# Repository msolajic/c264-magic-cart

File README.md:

# c264-magic-cart
Hardware design of a cartridge for the Commodore 264 series of computers - Commodore 16, 116 and plus/4

This is the hardware part that accompanies the project of [Magic Cartridge Generator](https://bitbucket.org/zzarko/magic-cartridge-generator/)

This project is free to use and you can use any PCB manufacturer by downloading the Gerber files, but if you would like to support my work and help with further hardware development you can order these PCBs on PCBWay trough this link:

You will get cheap and professionally made PCBs, I will get credits that will help with this and [other projects](https://www.pcbway.com/project/member/?bmbno=1DE407A1-1650-47). Also, if you have to register to that site, [you can use this link](https://pcbway.com/g/YFnBAc) to get bonus initial credit.

Hardware Description
--------------------

Original Commodore 264 cartridges could be up to 32 Kb in size, in two separate banks of 16Kb. This cartridge implements a latch which is tied to a memory address, so it can address (in this incarnation) up to 2 megabytes of data (128 banks of 16Kb). In that regard, it is very similar to Magic Desk or Ocean cartridges for the Commodore 64.

EPROM is selected by the C1LO selection line coming from the computer, and the 16k of data from the selected bank is visible in the memory map at addresses $8000 - $BFFF.

Inputs of an 8-bit latch (74LS273) are connected to the data lines. A GAL20V8 is responsible for decoding writes to a memory address by decoding the full address bus. Decoder has the option of decoding several frequently used addresses for banking cartridges, since there is no standard address defined. This cartridge is primarily designed to enable making onefile program compilations through the [Magic Cartridge Generator](https://bitbucket.org/zzarko/magic-cartridge-generator/).

The PCB was designed to accommodate various types of EPROMs and their FLASH variants. The smallest EPROM you can use is 27C010 (128Kb), and the largest is 27C160 (2Mb). There are two EPROM sockets, but you cannot use both at the same time. The left socket accepts standard 8-bit EPROMs and their FLASH variants (27C010 to 27C080) and the right socket is for 27C160 (16-bit EPROM in 8-bit mode).

Address decoder
---------------

The address decoder is implemented in GAL20V8. All 16 address lines, /PHI2 and /RW are connected to the GAL to enable single-address decoding. Of course, a GAL16V8 could have been used, but it would only be capable of decoding an address in 16-byte blocks, or the address decoder could be implemented in TTL logic which would require at least 3 ICs. Two spare inputs were used to create a selection jumper to select between four commonly used addresses for cartridge banking. The default address used is $FDFE, which is mentioned in the document at http://solder-synergy.de/plus4/hardware/makers/ioarea.txt as "Register on EPROM-card". Other addresses which can be configured are $FE00 (used on a Hungarian homebrew cartridge found at https://www.commodoreszerviz.hu/commodore_16-116-plus_4_1mb_cartridge_juhasz_jacint.htm), $FDA0 used by another homebrew cartridge, and $FD17 which is also mentioned in the document above as "Register for EPROM-/sRAM-expansion". 

The address decoder is configured with a solder-jumper on the bottom side of the PCB. The configuration legend is also shown at the bottom. Use extreme care when trying to bridge the pads (if needed, as the default configuration is already selected when the jumper is open) because you can easily lift the pads with excess heat.

EPROM selection jumpers
-----------------------

In order to support most common types of EPROMs and FLASH EPROMs, two solder jumpers have been placed on the bottom side of the PCB. They look like this:

These jumpers HAVE to be configured before plugging the cartridge to your computer! Different types of EPROMs and their FLASH variants have some pins swapped, and if you are using a chip smaller than the maximum size, the unused address lines have to be pulled high on the EPROM side to ensure proper functioning.

You can use either the left 32-pin socket, or the right 42-pin socket, but never the both at the same time. The right socket is meant for using the 2Mb 27C160 EPROMs. This is a 16-bit EPROM but it can be forced to work in 8-bit mode by connecting the BYTE/Vpp pin to ground. In that configuration, the address lines are shifted by one and the output Q15 is used as address line A0. These 16-bit EPROMs are not directly supported by the popular TL866 programmer, and have to be programmed through an adapter, in multiple passes. An example adapter can be found [here](https://github.com/mafe72/27c160-tl866-adapter) or [here](https://github.com/gaggi/27c160-tl866-adapter)

GAL programming
---------------

In the GAL folder there are both .pld and .jed files provided for GAL programming. You can also use a programmer such as TL866 to program the GAL. If you want to change anything in the decoder, you can use [GALASM](https://github.com/daveho/GALasm) to recompile the .pld file. 

Capacitors
----------

The capacitors are not needed, but you can populate them. They are 100nF 50V MLCC or ceramic capacitors with 2.54mm raster.

Enclosure compatibility
-----------------------

The PCB is designed to be as close in dimensions as the original Commodore PCB, so you can re-use an original Commodore cartridge case, or you can 3D-print one. Compatible designs are available on Thingiverse, such as [this one](https://www.thingiverse.com/thing:3657002) or [this one](https://www.thingiverse.com/thing:4627130). Unfortunately, no one makes injection-moulded cartridge cases for the 264 series anymore.

Revision history
----------------

- Rev.1
    - Initial release

Changelog
---------

- February 11th, 2022:
    - Added EAGLE schematic and board files
    
Thanks:
-------

My thanks go to:

- Žarko Živanov, for creating the Magic Cartridge Generator
- Everyone from [Plus/4 World](http://plus4world.powweb.com/) for help with hardware and software specifics
- Groepaz from the [VICE Team](https://vice-emu.sourceforge.io/), for adding the cartridge support in VICE (currently available only in nightly builds)
- Jim Drew and the CRX crew
- Everyone who ordered any of my PCBs from PCBWay
- and all other people in the Commodore 64 community that I forgot to mention, you guys are awesome!

License
-------
c264-magic-cart is Open Hardware licensed under the [CERN OHL v. 1.2](http://ohwr.org/cernohl), released by Marko Šolajić in 2021. You may redistribute and modify this documentation under the terms of the CERN OHL v.1.2.

A copy of the full license is included in file [LICENSE.txt](LICENSE.txt)

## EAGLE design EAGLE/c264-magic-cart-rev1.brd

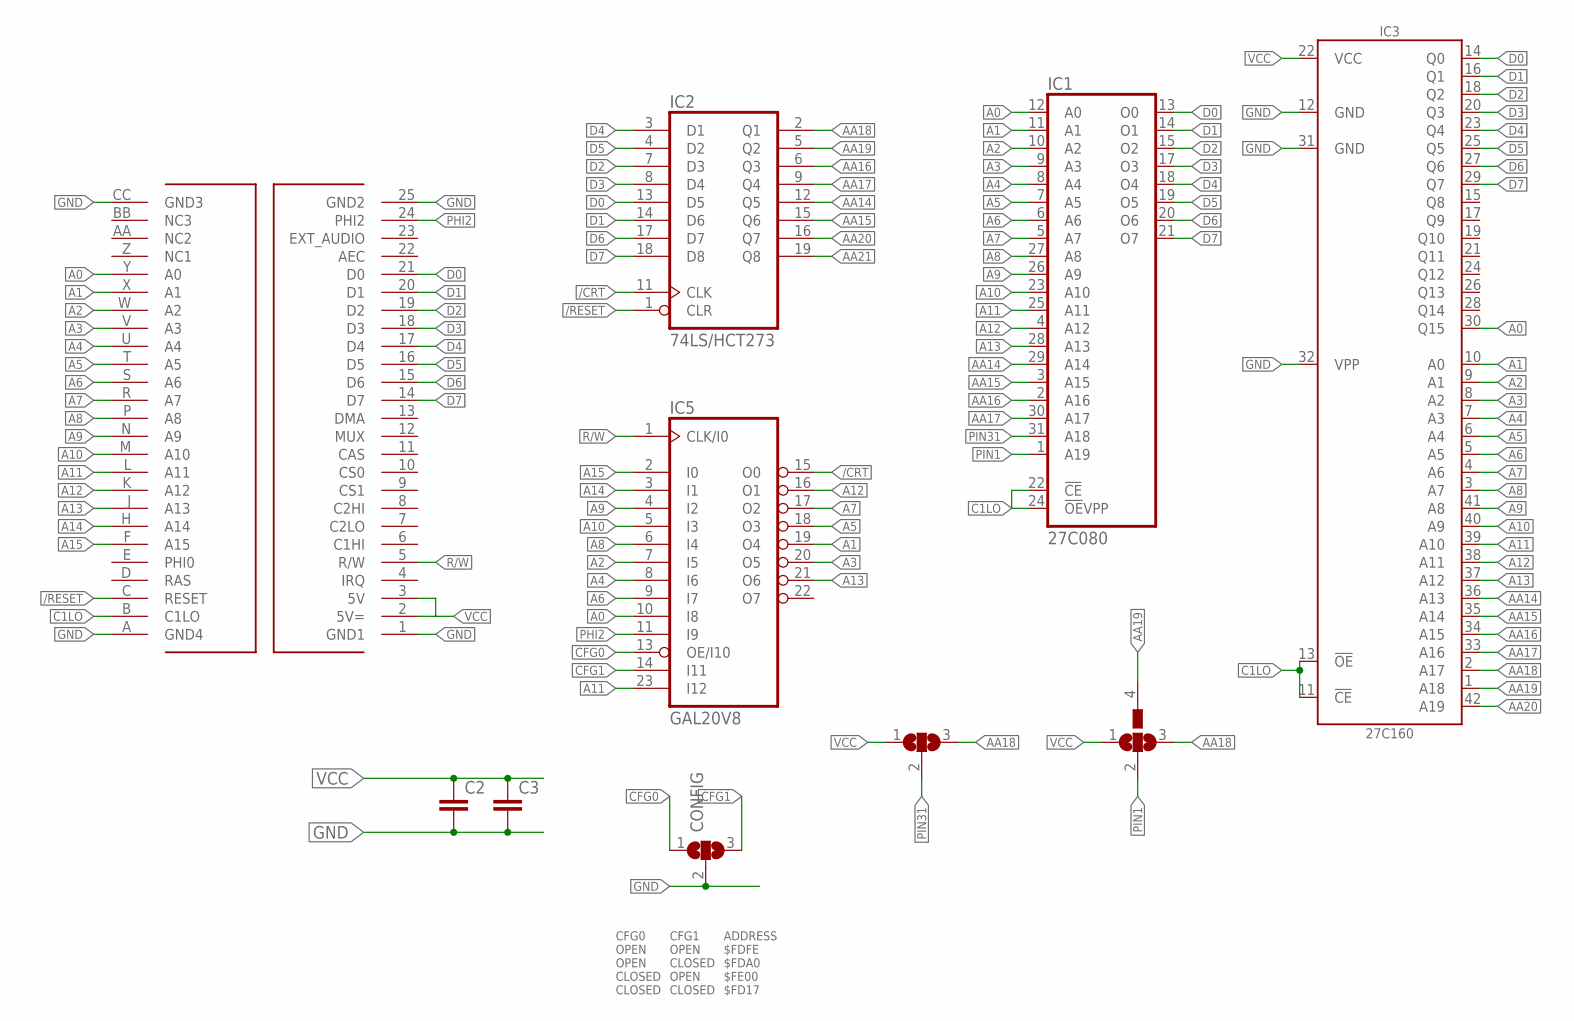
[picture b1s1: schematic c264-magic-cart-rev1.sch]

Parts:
C2, C3: C-EU025-024X044; C025-024X044
CONFIG: SJ2W; SJ_2
IC1: 27C080; DIL32
IC2: 74LS/HCT273; DIL20
IC3: 27C160; DIP42
IC5: GAL20V8; DIL24-3
SJ1: SJ2W; SJ_2
U$1: C16_CARTRIDGE; C16_CART
U$2: SJ3; SJ_3

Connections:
/CRT: IC2.11 (CLK), IC5.15 (O0)
/RESET: IC2.1 (CLR), U$1.C (RESET)
A0: IC1.12 (A0), IC3.30 (Q15), IC5.10 (I8), U$1.Y (A0)
A1: IC1.11 (A1), IC3.10 (A0), IC5.19 (O4), U$1.X (A1)
A2: IC1.10 (A2), IC3.9 (A1), IC5.7 (I5), U$1.W (A2)
A3: IC1.9 (A3), IC3.8 (A2), IC5.20 (O5), U$1.V (A3)
A4: IC1.8 (A4), IC3.7 (A3), IC5.8 (I6), U$1.U (A4)
A5: IC1.7 (A5), IC3.6 (A4), IC5.18 (O3), U$1.T (A5)
A6: IC1.6 (A6), IC3.5 (A5), IC5.9 (I7), U$1.S (A6)
A7: IC1.5 (A7), IC3.4 (A6), IC5.17 (O2), U$1.R (A7)
A8: IC1.27 (A8), IC3.3 (A7), IC5.6 (I4), U$1.P (A8)
A9: IC1.26 (A9), IC3.41 (A8), IC5.4 (I2), U$1.N (A9)
A10: IC1.23 (A10), IC3.40 (A9), IC5.5 (I3), U$1.M (A10)
A11: IC1.25 (A11), IC3.39 (A10), IC5.23 (I12), U$1.L (A11)
A12: IC1.4 (A12), IC3.38 (A11), IC5.16 (O1), U$1.K (A12)
A13: IC1.28 (A13), IC3.37 (A12), IC5.21 (O6), U$1.J (A13)
A14: IC5.3 (I1), U$1.H (A14)
A15: IC5.2 (I0), U$1.F (A15)
AA14: IC1.29 (A14), IC2.12 (Q5), IC3.36 (A13)
AA15: IC1.3 (A15), IC2.15 (Q6), IC3.35 (A14)
AA16: IC1.2 (A16), IC2.6 (Q3), IC3.34 (A15)
AA17: IC1.30 (A17), IC2.9 (Q4), IC3.33 (A16)
AA18: IC2.2 (Q1), IC3.2 (A17), SJ1.3, U$2.3
AA19: IC2.5 (Q2), IC3.1 (A18), U$2.4
AA20: IC2.16 (Q7), IC3.42 (A19)
AA21: IC2.19 (Q8)
C1LO: IC1.22 (!CE), IC1.24 (!OE!VPP), IC3.11 (!CE), IC3.13 (!OE), U$1.B (C1LO)
CFG0: CONFIG.1, IC5.13 (OE/I10)
CFG1: CONFIG.3, IC5.14 (I11)
D0: IC1.13 (O0), IC2.13 (D5), IC3.14 (Q0), U$1.21 (D0)
D1: IC1.14 (O1), IC2.14 (D6), IC3.16 (Q1), U$1.20 (D1)
D2: IC1.15 (O2), IC2.7 (D3), IC3.18 (Q2), U$1.19 (D2)
D3: IC1.17 (O3), IC2.8 (D4), IC3.20 (Q3), U$1.18 (D3)
D4: IC1.18 (O4), IC2.3 (D1), IC3.23 (Q4), U$1.17 (D4)
D5: IC1.19 (O5), IC2.4 (D2), IC3.25 (Q5), U$1.16 (D5)
D6: IC1.20 (O6), IC2.17 (D7), IC3.27 (Q6), U$1.15 (D6)
D7: IC1.21 (O7), IC2.18 (D8), IC3.29 (Q7), U$1.14 (D7)
GND: C2.2, C3.2, CONFIG.2, IC1.16 (GND), IC2.10 (GND), IC3.12 (GND), IC3.31 (GND), IC3.32 (VPP), IC5.12 (GND), U$1.1 (GND1), U$1.25 (GND2), U$1.A (GND4), U$1.CC (GND3)
PHI2: IC5.11 (I9), U$1.24 (PHI2)
PIN1: IC1.1 (A19), U$2.2
PIN31: IC1.31 (A18), SJ1.2
R/W: IC5.1 (CLK/I0), U$1.5 (R/W)
VCC: C2.1, C3.1, IC1.32 (VCC), IC2.20 (VCC), IC3.22 (VCC), IC5.24 (VCC), SJ1.1, U$1.2 (5V=), U$1.3 (5V), U$2.1

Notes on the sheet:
CFG0 OPEN OPEN CLOSED CLOSED
CFG1 OPEN CLOSED OPEN CLOSED
ADDRESS $FDFE $FDA0 $FE00 $FD17

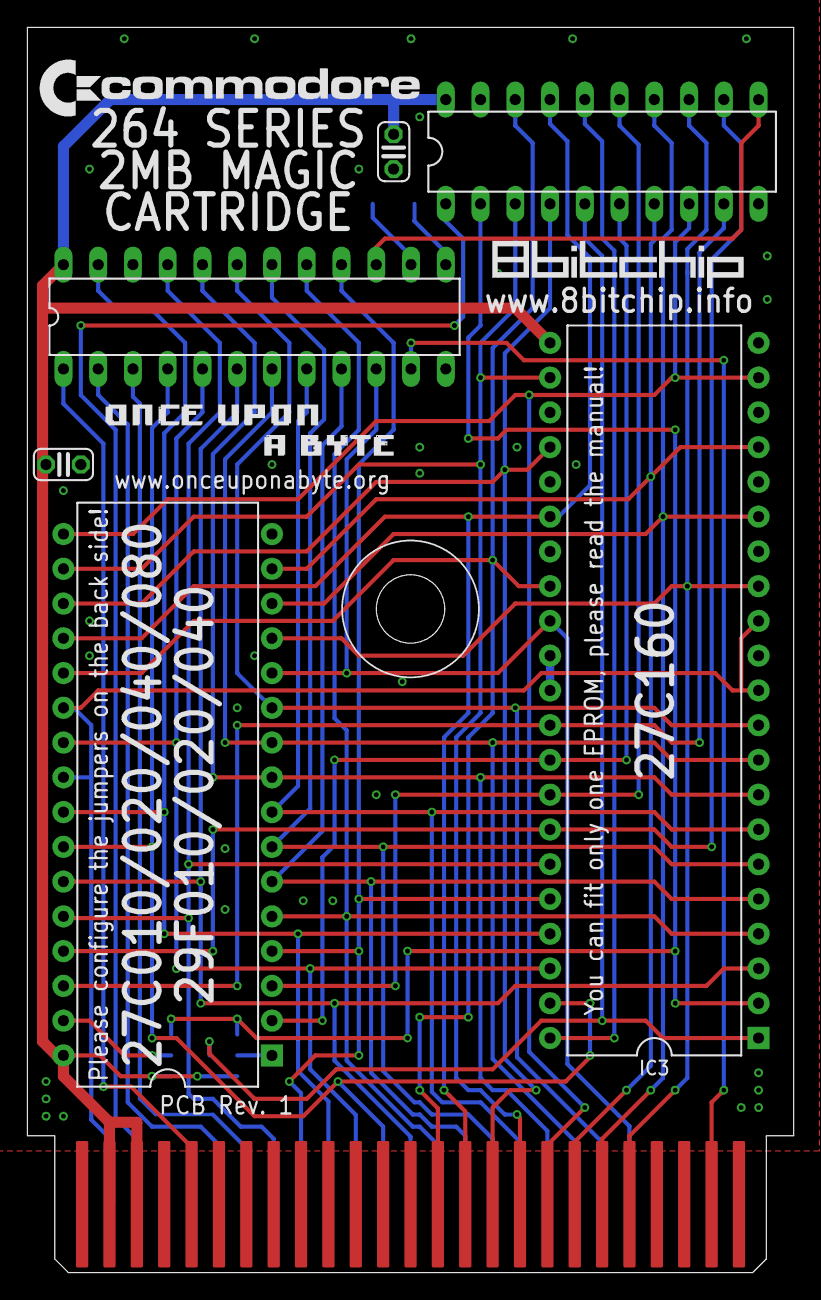
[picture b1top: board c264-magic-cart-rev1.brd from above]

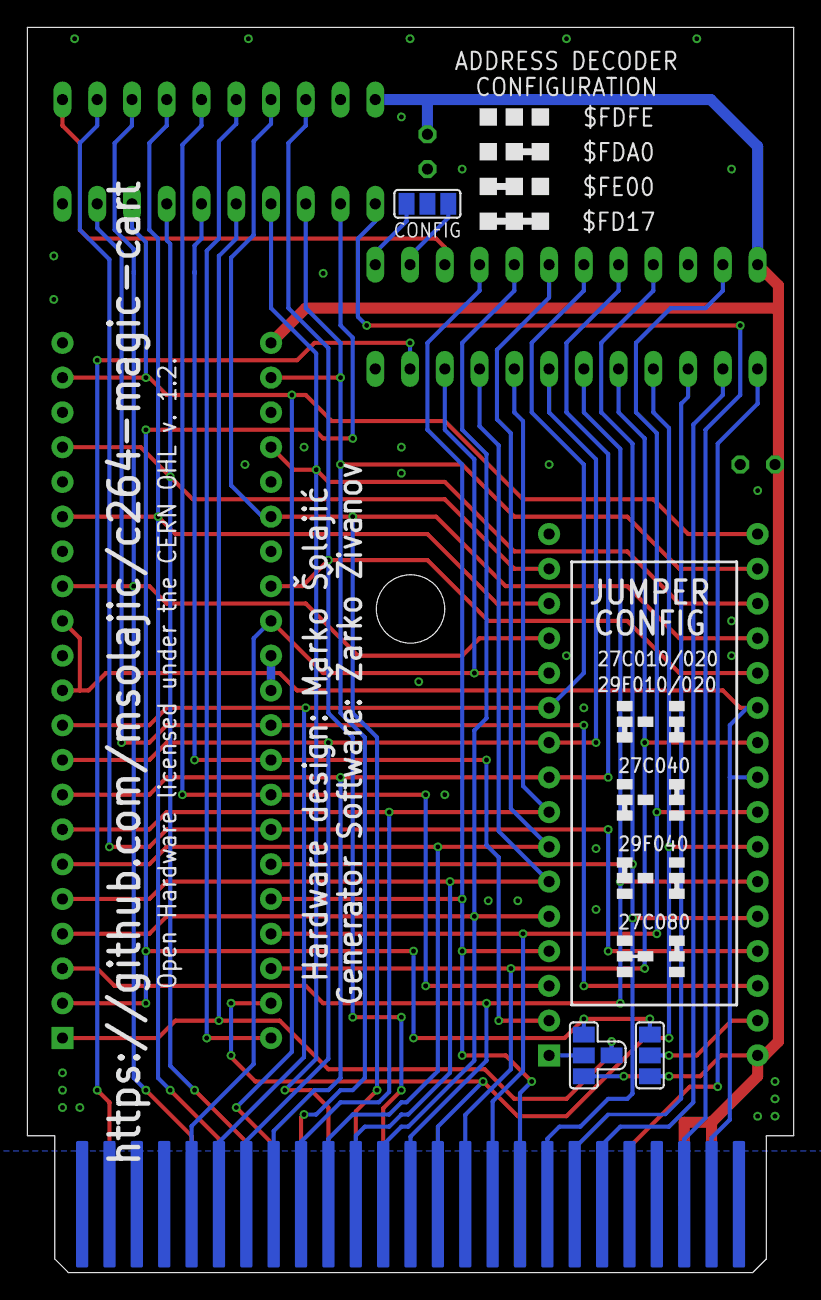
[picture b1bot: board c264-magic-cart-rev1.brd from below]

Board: 2 copper layers, 56.0 x 91.0 mm, 10 parts (3 on the bottom side), 42 nets.

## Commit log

2021-09-10 Updated dead links
2022-02-10 Added EAGLE schematic and board file
